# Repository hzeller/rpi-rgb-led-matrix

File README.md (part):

Controlling RGB LED display with Raspberry Pi GPIO
==================================================

A library to control commonly available 128x64, 64x64, 32x32 or 16x32 RGB LED panels
with the Raspberry Pi. Can support PWM up to 11Bit per channel, providing
true 24bpp color with CIE1931 profile.

Supports 3 chains with many panels each on a regular Pi.
On a Raspberry Pi 2 or 3, you can easily chain 12 panels in that chain
(so 36 panels total), but you can theoretically stretch that to up
to 96-ish panels (32 chain length) and still reach
around 100Hz refresh rate with full 24Bit color (theoretical - never tested
this; there might likely be timing problems with the panels that will creep
up then).

With fewer colors or so-called 'outdoor panels' you can control even more,
faster.

The LED-matrix library is (c) Henner Zeller <h.zeller@acm.org>, licensed with
[GNU General Public License Version 2.0 (or any later version)](http://www.gnu.org/licenses/gpl-2.0.txt)
(which means, if you use it in a product somewhere, you need to make the
source and all your modifications available to the receiver of such product so
that they have the freedom to adapt and improve).
Yes, you are also allowed to use
this code under the [GNU General Public License Version 3.0](http://www.gnu.org/licenses/gpl-3.0.txt)
which allows linking with Apache 2.0 code and LGPL-3.0 code.

## Discourse discussion group

**If you'd like help, please do not file a bug, use the discussion board instead:**
https://rpi-rgb-led-matrix.discourse.group/  (obviously please read this whole page first).
If you file a bug asking for personal help instead of using the discourse group, please
state in your bug that you have read this entire page and that you're indeed filing a bug
or request for improvement. Otherwise, please use the discourse group.

Overview
--------
The RGB LED matrix panels can be scored at [Sparkfun][sparkfun],
[AdaFruit][ada] or eBay and Aliexpress. If you are in China, I'd try to get
them directly from some manufacturer, Taobao or Alibaba.

The `RGBMatrix` class provided in `include/led-matrix.h` does what is needed
to control these. You can use this as a library in your own projects or just
use the demo binary provided here which provides some useful examples.

Check out [utils/ directory for some ready-made tools](./utils) to get started
using the library, or the [examples-api-use/](./examples-api-use) directory if
you want to get started programming your own utils.

Panels supported
----------------
This library does not support PWM panels (which actually are better, but need
a completely different driver).\
It should support most other panels with direct addressing (3 to 5 address lines,
ABC for 8x2=16 lines, ABCD for 16x2=32 lines, and ABCDE for 32x2=64 lines).
It also supports panels using shift registers for line addressing, also called ABC
panels up to 64 lines.\
However some amount of panels have uncommon pixel layouts, especially the brighter
panels and may require special pixel mappers (some are called zigzag or zagzig, see
https://rpi-rgb-led-matrix.discourse.group/t/p10rgb-3535-4s-zaggiz-1-4scan-abc-p10-panels-and-https-github-com-2dom-pxmatrix/921 )

Until this wiki has its own confirmed list of working panels, you can refer to
this list: https://github.com/board707/DMD_STM32/wiki/Led_drivers and assume
that all supported panels there should work with this library, or could work
with minimal work to create a pixel mapper.
Please do refer to --led-multiplexing=<0..17> mentioned below and try all values. \
2025/11 update: DMD_STM32 has started adding experimental support for some PWM panels.
These should be labelled as "special" in the table above. They are not supported by this
lib, as it only supports non PWM panels (until someone contributes PWM support).

PWM/E-PWM/S-PWM Panels
----------------------
Newer PWM panels are not currently supported by this lib, but support would really be appreciated.
- https://github.com/hzeller/rpi-rgb-led-matrix/issues/466 - Master bug tracking PWM efforts
- https://github.com/hzeller/rpi-rgb-led-matrix/issues/1866 - Continued discussion

Some experimentation and success has been made with the following fork. Some panel support with FM6373, FM6363, SM16380SH
- https://github.com/kingdo9/rpi-rgb-led-matrix_pwm_experiment

Raspberry Pi 1-5 supported
------------------------------
This library supports the old Raspberry Pi's Version 1 with 26 pin header and
also the B+ models, the Pi Zero, Raspberry Pi 2,3,4 and 5 with 40 pins, as well
as the Compute Modules which have 44 GPIOs.

#### Raspberry Pi 5 support has now been added.
There are two modes to run this on the Pi 5 

**--led-rp1-rio=0** - Uses the Pi 5 coprocessor RP1 to perform the work (default) - Very minimal CPU usage

**--led-rp1-rio=1** - Uses Registered IO block of RP1 to communicate with the GPIO - Higher CPU usage but much faster performance.\
**NOTE: --led-slowdown-gpio** can have the opposite effect in this mode, so going from 2 to 3 may increase performance slightly with --led-rp1-rio=1.

Pi 5 Discussion -  https://github.com/hzeller/rpi-rgb-led-matrix/issues/1603

Thanks to contributions from the following libraries to help implement this.
https://github.com/adafruit/Adafruit_Blinka_Raspberry_Pi5_Piomatter \
https://github.com/bitslip6/rpi-gpu-hub75-matrix \
https://www.i-programmer.info/programming/148-hardware/16887-raspberry-pi-iot-in-c-pi-5-memory-mapped-gpio.html

The 26 pin models can drive one chain of RGB panels, the 40 pin models
**up to three** chains in parallel (each chain 12 or more panels long).
The Compute Module can drive **up to 6 chains in parallel**.
The Raspberry Pi 2 and 3 are faster and generally preferred to the older
models (and the Pi Zero). With the faster models, the panels sometimes
can't keep up with the speed; check out
this [troubleshooting section](#troubleshooting) what to do.

A lightweight, non-GUI, distribution such as [DietPi] is recommended.
[Raspbian Lite][raspbian-lite] is a bit easier to get started with and
is a good second choice.

Types of Displays
-----------------
There are various types of displays that come all with the same Hub75 connector.
They vary in the way the multiplexing is happening so this library supports
options to choose that.
All these are configured by flags (or, programmatically, in an [Options struct](include/led-matrix.h#L57)).

If you have a 64x32 display, you need to supply the flags
`--led-cols=64 --led-rows=32` for instance.

Depending on the Matrix, there are various configuration options that
you might need to set for it to work. See further below in the README for the
[detailed description of these](#changing-parameters-via-command-line-flags).
While the `--led-rows` and `--led-cols` can be derived from simply looking
at the panels, the other options might require some experimenting to find the
right setting if there is no description provided by the manufacturer of
the panel. Going through these options for experiments would typically not do
harm, so you're free to experiment to find your setting.

Flag                                | Description
:---------------      | :-----------------
`--led-cols`          | Columns in the LED matrix, the 'width'.
`--led-rows`          | Rows in the LED matrix, the 'height'.
`--led-multiplexing`  | In particular bright outdoor panels with small multiplex ratios require this. Often an indicator: if there are fewer address lines than expected: ABC (instead of ABCD) for 32 high panels and ABCD (instead of ABCDE) for 64 high panels.
`--led-row-addr-type` | Addressing of rows; in particular panels with only AB address lines might indicate that this is needed.
`--led-panel-type`    | Chipset of the panel. In particular if it doesn't light up at all, you might need to play with this option because it indicates that the panel requires a particular initialization sequence.

Panels can be chained by connecting the output of one panel to the input of
the next panel. You can chain quite a few together, but the refresh rate will
reduce with longer chains.

The 64x64 matrixes typically come in two kinds: with 5 address
lines (A, B, C, D, E), or (A, B); the latter needs a `--led-row-addr-type=1`
parameter. So-called 'outdoor panels' are typically brighter and allow for
faster refresh-rate for the same size, but do some multiplexing internally
of which there are a few types out there; they can be chosen with
the `--led-multiplexing` parameter.
Many 128x64 panels now use ABC addressing using shift registers, instead of direct
ABCDE addressing. Look at using --led-row-addr-type=5 or --led-row-addr-type=3
with them (and you may need to use --led-slowdown-gpio of 2 or more. Please
see this bug for more details: https://github.com/hzeller/rpi-rgb-led-matrix/issues/1774

There are some panels that have a different chip-set than the default HUB75.
These require some initialization sequence. The current supported types are
`--led-panel-type=FM6126A` and `--led-panel-type=FM6127`.

Generally, the higher scan-rate (e.g. 1:8), a.k.a. outdoor panels generally
allow faster refresh rate, but you might need to figure out the multiplexing
mapping if one of the three provided does not work.

Some 32x16 outdoor matrixes with 1:4 scan (e.g. [Qiangli Q10(1/4) or X10(1/4)](http://qiangliled.com/products-63.html))
have 4 address line (A, B, C, D). For such matrices is necessary to
use `--led-row-addr-type=2` parameter. Also the matrix Qiangli Q10(1/4)
have "Z"-stripe pixel mapping and in this case, you'd use two parameters
at the same time `--led-row-addr-type=2 --led-multiplexing=4`.

Sub-Pages
---------
This documentation is split into parts that help you through the process

- 
    [**Wire up the matrix to your Pi**](./wiring.md). This document describes
    what goes where.
- [How to map pixels between panels or within panels](./lib). This is crucial for figuring out pixel mappers,
  matrix mappers and so forth. This is where you will learn about panel layout with U-Mapper, V-Mapper, V-Mapper:Z
- [Adapter GPIO boards output to up to 3 channels (electrodragon board recommended)](./adapter).
    If you have an [Adafruit HAT] or [Adafruit Bonnet], you can choose that with
    a command line option [described below](#if-you-have-an-adafruit-hat-or-bonnet)
- [All the command line options you can give to demo and in turn use in your library code](./examples-api-use).
- [Installing an Optimized Kernel to fix most flickering issues](./optimized-kernel)

Python Support
--------------
The python bindings have been overhauled as of February 2026 and are now built with scikit-build-core and cmake. While
this update has been tested there are likely edge cases that have not been caught. Please subscribe to the master Python
bug to assist or check for the latest updates.
https://github.com/hzeller/rpi-rgb-led-matrix/issues/1749.

The entire repository itself is PIP-able and can be installed as a package directly. Python dev packages are required.
```
sudo apt-get install python-dev-is-python3 python3-pil cython3
pip install git+https://github.com/hzeller/rpi-rgb-led-matrix
```

Rpi Hardware Support
--------------------
While this code should still work on rPi1 or Rpi0, those are underpowered and not recommended. An ESP32 is cheaper and faster.
Rpi2 is honestly old and slow too.
Rpi3 / Rpi3a / Rpi0 2wl will work for most displays but will be slow if you are rotating a huge display in a mapper (Rpi0 2wl is a slightly faster version of Rpi3)
Rpi4 is the fastest supported chip which will need a higher slowdown gpio value to avoid overwhelming panels (if they display garbage)
Rpi5 is not officially supported as of 2025/11, but see https://github.com/hzeller/rpi-rgb-led-matrix/issues/1603

Let's do it
------------
  1. Run a demo. You find that in the
     [examples-api-use/](./examples-api-use#running-some-demos) directory:
```
make -C examples-api-use
sudo examples-api-use/demo -D0
```
  2. Use the utilities. The [utils](./utils) directory has some ready-made
    useful utilities to show content. [Go there](./utils) to see how to
    compile and run these.
  3. Write your own programs using the Matrix in C++ or one of the
     bindings such as Python or C#.

### Wiring / Boards

Please see the [Adadpter Boards or Self Wiring](./adapter).

Summary is:
- Yes you can self wire without level shifters and it will work most of the time, but if you're not in a hurry get a board
- https://www.electrodragon.com/product/rgb-matrix-panel-drive-board-for-raspberry-pi-v2/ **is the recommended solution with 3 channels and level shifters**. You can't go wrong there, but expect a bit of shipping time.
- If shipping time is crucial and you don't want to wire your own, Adafruit sells a single channel board (the electrodragon one is 3 channels), but note that its wiring is non standard and requires a special compile option or command line argument: https://www.adafruit.com/product/3211

### Utilities

The [utils directory](./utils) is meant for ready utilities to show images or
animated gifs or videos. Read the [README](./utils/README.md) there for
instructions how to compile.

There are external projects that use this library and provide higher level
network protocols, such as the
 * [FlaschenTaschen implementation](https://github.com/hzeller/flaschen-taschen)
   (VLC can send videos to it natively)
 * [PixelPusher implementation](https://github.com/hzeller/rpi-matrix-pixelpusher) (common in light art installations)
 * [ZeroMQ-server](https://github.com/Knifa/led-matrix-zmq-server) to receive
   content.
 * Marc's [FastLED_RPIRGBPanel_GFX](http://marc.merlins.org/perso/arduino/post_2020-01-01_Running-FastLED_-Adafruit_GFX_-and-LEDMatrix-code-on-High-Resolution-RGBPanels-with-a-Raspberry-Pi.html) allows running arduino code on linux/rPi and display on bigger RGBPanel matrices than arduino chips, can.

### API

The library comes as an API that you can use for your own utilities and use-cases.

  * The native library is a C++ library (see [include/](./include)).
    Example uses you find in the [examples-api-use/](./examples-api-use)
    directory.
  * If you prefer to program in C, there is also a
    [C API](./include/led-matrix-c.h).
  * In the [python](./bindings/python) subdirectory, you find a Python API including a
    couple of [examples](./bindings/python/samples) to get started.
  * There are a couple of external bindings, such as
      * [Nodejs binding] by Maxime Journaux
      * [Nodejs/Typescript binding] by Alex Eden
      * [Go binding] by Máximo Cuadros
      * [Rust binding] by Vincent Pasquier

### Changing parameters via command-line flags

For the programs in this distribution and also automatically in your own
programs using this library, there are a lot of parameters provided as command
line flags, so that you don't have to re-compile your programs to tweak them.
Some might need to be changed for your particular kind of panel.

Here is a little run-down of what these command-line flags do and when you'd
like to change them.

First things first: if you have a different wiring than described in
[wiring](./wiring.md), for instance if you have an Adafruit HAT/Bonnet, you can
choose these here:

```
--led-gpio-mapping=<gpio-mapping>: Name of GPIO mapping used. Default "regular"
```

This can have values such as
  - `--led-gpio-mapping=regular` The standard mapping of this library, described in the [wiring](./wiring.md) page.
  - `--led-gpio-mapping=adafruit-hat` The Adafruit HAT/Bonnet, that uses this library or
  - `--led-gpio-mapping=adafruit-hat-pwm` Adafruit HAT with the anti- hardware mod [described below](#improving-flicker-hardware-patch).
  - `--led-gpio-mapping=compute-module` Additional 3 parallel chains can be used with the Compute Module.

Learn more about the mappings in the [wiring documentation](wiring.md#alternative-hardware-mappings).

#### GPIO speed

```
--led-slowdown-gpio=<0..10>: Slowdown GPIO. Needed for faster Pis and/or slower panels (Default: 1).
```

The Raspberry Pi starting with Pi2 are putting out data too fast for almost
all LED panels I have seen. In this case, you want to slow down writing to
GPIO. Zero for this parameter means 'no slowdown'.

The default 1 (one) typically works fine, but often you have to even go further
by setting it to 2 (two). If you have a Raspberry Pi with a slower processor
(Model A, A+, B+, Zero), then a value of 0 (zero) might work and is desirable.

If you find yourself needing very high values of slowdown like 8 for ABC 128x64 panels,
do try --led-row-addr-type=5 instead of --led-row-addr-type=3. Details in this bug:
https://github.com/hzeller/rpi-rgb-led-matrix/issues/1773

A Raspberry Pi 3 or Pi4 might even need higher values for the panels to be
happy.

#### Panel Connection
The next most important flags describe the type and number of displays connected

```
--led-rows=<rows>        : Panel rows. Typically 8, 16, 32 or 64. (Default: 32).
--led-cols=<cols>        : Panel columns. Typically 32 or 64. (Default: 32).
--led-chain=<chained>    : Number of daisy-chained panels. (Default: 1).
--led-parallel=<parallel>: For A/B+ models or RPi2,3b: parallel chains. range=1..3 (Default: 1, 6 for Compute Module).
```

These are the most important ones: here you choose how many panels you have
connected and how many rows are in each panel. Panels can be chained (each panel
has an input and output connector, see the
[wiring documentation](wiring.md#chains)) -- the `--led-chain` flag tells the
library how many panels are chained together. The newer Raspberry Pi's allow
to connect multiple chains in parallel, the `--led-parallel` flag tells it how
many there are.

This illustrates what each of these parameters mean:

##### Panel Type

Typically, panels should just work out of the box, but some panels use a
different chip-set that requires some initialization. If you don't see any
output on your panel, try setting:

```
--led-panel-type=FM6126A
```

Some panels have the FM6127 chip, which is also an option.

##### Multiplexing
If you have some 'outdoor' panels or panels with different multiplexing,
the following will be useful:

```
--led-multiplexing=<0..17> : Mux type: 0=direct; 1=Stripe; 2=Checkered...
```

The outdoor panels have different multiplexing which allows them to be faster
and brighter, but by default their output looks jumbled up.
They require some pixel-mapping of which there are a few
types you can try and hopefully one of them works for your panel; The default=0
is no mapping ('standard' panels), while 1, 2, ... are different mappings
to try with. If your panel has a different mapping, you find everything you
need to implement one in [lib/multiplex-mappers.cc](lib/multiplex-mappers.cc).
Please send a pull request if you encounter a panel for which you needed to
implement a new mapping.

Note that you have to set the `--led-rows` and `--led-cols` to the rows and
columns that are physically on each chained panel so that the multiplexing
option can work properly. For instance a `32x16` panel with `1:4` multiplexing
would be controlled with `--led-rows=16 --led-cols=32 --led-multiplexing=1` (or
whatever multiplexing type your panel is, so it can also be `--led-multiplexing=2` ...).

For `64x32` panels with `1:8` multiplexing, this would typically be
`--led-rows=32 --led-cols=64 --led-multiplexing=1`;
however, there are some panels that internally behave like
two chained panels, so then you'd use
`--led-rows=32 --led-cols=32 --led-chain=2 --led-multiplexing=1`;

```
--led-row-addr-type=<0..5>: 0 = default; 1 = AB-addressed panels; 2 = direct row select; 3 = ABC-addressed panels; 4 = ABC Shift + DE direct, 5 = ABC method similar to 3, but faster on some panels (needs less of a slowdown) (Default: 0).
```

This option is useful for certain 64x64 or 32x16 panels. For 64x64 panels,
that only have an `A` and `B` address line, you'd use `--led-row-addr-type=1`.
This is only tested with one panel so far, so if it doesn't work for you,
please send a pull request.

For 32x16 outdoor panels, that have have 4 address line (A, B, C, D), it is
necessary to use `--led-row-addr-type=2`.

Performance improvements and limits, Maximizing refresh rate, ABC vs ABCDE, row-addr-type=5 vs 3
-------------------------------------------------------------------------------------------------
Regardless of which driving hardware you use, ultimately you can only push pixels
so fast to a string of panels before you get flickering due to too low a refresh
rate (less than 80-100Hz), or before you refresh the panel lines too fast and they
appear too dim because each line is not displayed long enough before it is turned off.

Basic performance tips:
- Use --led-show-refresh to see the refresh rate while you try parameters
- use an active-3 board with led-parallel=3 any time possible instead of chaining panels.
- led-pwm-dither-bits=1 gives you a speed boost but potentially less brightness
- led-pwm-lsb-nanoseconds=50 also gives you a speed boost but may lead to less brightness
- led-pwm-bits=7 or even lower decrease color depth but increases refresh speed
- AB panels and other panels with that use values of led-multiplexing bigger than 0,
will also go faster, although as you tune more options given above, their advantage will decrease.
- 32x16 ABC panels are faster than ABCD which are faster than ABCDE, which are faster than 128x64 ABC panels
(which do use 5 address lines, but over only 3 wires)
- For 128x64 ABC speed on shift registers vs ABCDE
- Use at least an rPi3 (rPi4 is still slightly faster but may need --led-slowdown-gpio=2)

Maximizing refresh rate to 300 or even 400Mhz refresh for 3x 128x64 panels:
- ABCDE panels will allow for faster refresh rate than ABC panels because they can be run with
lower --led-slowdown-gpio=1 (which may need to be 2 for ABCDE) on rPi3 (rPi4 may require bigger
slowdowns. You may even end up in a situation where a Pi3 will give you faster refresh than a Pi4
by needing smaller slowdowns
- To achieve 410Hz refresh for 3x 128x64 direct ABCDE panels, use this "~/rpi-rgb-led-matrix/examples-api-use/demo --led-rows=64 --led-cols=128 --led-chain=1 --led-parallel=3 --led-show-refresh --led-scan-mode=0 --led-pwm-bits=7 --led-pwm-lsb-nanoseconds=50 --led-pwm-dither-bits=1 -D0  --led-row-addr-type=0 --led-slowdown-gpio=1"
- To achieve 350hz refresh for 3x 128x64 shift register panels, use this: "~/rpi-rgb-led-matrix/examples-api-use/demo --led-rows=64 --led-cols=128 --led-chain=1 --led-parallel=3 --led-show-refresh --led-scan-mode=0 --led-pwm-bits=7 --led-pwm-lsb-nanoseconds=50 --led-pwm-dither-bits=1 -D0  --led-row-addr-type=5 --led-slowdown-gpio=2"

Please see this bug for discussion of ABC vs ABCDE and using --led-row-addr-type=5 instead of --led-row-addr-type=3:
https://github.com/hzeller/rpi-rgb-led-matrix/issues/1774#issuecomment-2860617056

Maximum resolutions reasonably achievable:
A general rule of thumb is that running 16K pixels (128x128 or otherwise) on a single chain,
is already pushing limits and you will have to make tradeoffs in visual quality. 32K pixels
(like 128x256) is definitely pushing things and you'll get 100Hz or less depending on the
performance options you choose.
This puts the maximum reasonable resolution around 100K pixels (like 384x256) for 3 chains.
You can see more examples and video capture of speed on [Marc MERLIN's page 'RGB Panels, from 192x80, to 384x192, to 384x256 and maybe not much beyond'](http://marc.merlins.org/perso/arduino/post_2020-03-13_RGB-Panels_-from-192x80_-to-384x192_-to-384x256-and-maybe-not-much-beyond.html)
If your refresh rate is below 300Hz, expect likely black bars when taking cell phone pictures.
A real camera with shutter speed lowered accordingly, will get around this.

Ultimately, you should not expect to go past 64K pixels using 3 chains without significant
quality tradeoffs. If you need bigger displays, you should use multiple boards and synchronize the
output.

#### Panel Arrangement

```
--led-pixel-mapper  : Semicolon-separated list of pixel-mappers to arrange pixels.
```

Optional params after a colon e.g. "U-mapper;Rotate:90"

Available | Parameter after colon| Example
----------|----------------------|----------
Mirror    | `H` or `V` for horizontal/vertical mirror. | `Mirror:H`
Rotate    | Degrees.                                   | `Rotate:90`
U-mapper  | -

Mapping the logical layout of your boards to your physical arrangement. See
more in [Remapping coordinates](./examples-api-use#remapping-coordinates).

#### Misc Options

```
--led-brightness=<percent>: Brightness in percent (Default: 100).
```

Self explanatory.

```
--led-pwm-bits=<1..11>    : PWM bits (Default: 11).
```

The LEDs can only be switched on or off, so the shaded brightness perception
is achieved via PWM (Pulse Width Modulation). In order to get a good 8 Bit
per color resolution (24Bit RGB), the 11 bits default per color are good
(why ? Because our eyes are actually perceiving brightness logarithmically, so
we need a lot more physical resolution to get 24Bit sRGB).

With this flag, you can change how many bits it should use for this; lowering it
means the lower bits (=more subtle color nuances) are omitted.
Typically you might be mostly interested in the extremes: 1 Bit for situations
that only require 8 colors (e.g. for high contrast text displays) or 11 Bit
for everything else (e.g. showing images or videos). Why would you bother at all ?
Lower number of bits use slightly less CPU and result in a higher refresh rate.

```
--led-show-refresh        : Show refresh rate.
```

This shows the current refresh rate of the LED panel, the time to refresh
a full picture. Typically, you want this number to be pretty high, because the
human eye is pretty sensitive to flicker. Depending on the settings, the
refresh rate with this library are typically in the hundreds of Hertz but
can drop low with very long chains. Humans have different levels of perceiving
flicker - some are fine with 100Hz refresh, others need 250Hz.
So if you are curious, this gives you the number (shown on the terminal).

The refresh rate depends on a lot of factors, from `--led-rows` and `--led-chain`
to `--led-pwm-bits`, `--led-pwm-lsb-nanoseconds` and `--led-pwm-dither-bits`.
If you are tweaking these parameters, showing the refresh rate can be a
useful tool.

```
--led-limit-refresh=<Hz>  : Limit refresh rate to this frequency in Hz. Useful to keep a
                            constant refresh rate on loaded system. 0=no limit. Default: 0
```

This allows to limit the refresh rate to a particular frequency to approach
a fixed refresh rate.

This can be used to mitigate some situations in which you have a faint flicker,
which can happen due to hardware events (network access)
or other situations such as other IO or heavy memory access by other
processes. Also when you see wildly changing refresh frequencies with
`--led-show-refresh`.

You trade a slightly slower refresh rate and display brightness for less
visible flicker situations.

For this to calibrate, run your program for a while with --led-show-refresh
and watch the line that shows the current refresh rate and minimum refresh
rate observed. So wait a while until that value doesn't
change anymore (e.g. a minute, so that you catch tasks that happen once
a minute, such as ntp updated).
Use this as a guidance what value to choose with `--led-limit-refresh`.

The refresh rate will now be adapted to always reach this value
between frames, so faster refreshes will be slowed down, but the occasional
delayed frame will fit into the time-window as well, thus reducing visible
brightness fluctuations.

You can play with value a little and reduce until you find a good balance
between refresh rate and flicker suppression.

Use this also if you want to have a stable baseline refresh rate when using
the vsync-multiple flag `-V` in the [led-image-viewer] or
[video-viewer] utility programs.

```
--led-no-busy-waiting     : Don't use busy waiting when limiting refresh rate.
```

This allows to switch from busy waiting to sleep waiting when limiting the
refresh rate (`--led-limit-refresh`).

By default, refresh rate limiting uses busy waiting, which is CPU intensive but
gives most accurate timings. This is fine for multi-core boards.

On single core boards (e.g.: Raspberry Pi Zero) busy waiting makes the system
unresponsive for other/background tasks. There, sleep waiting improves the
system's responsiveness at the cost of slightly less accurate timings.

```
--led-scan-mode=<0..1>    : 0 = progressive; 1 = interlaced (Default: 0).
```

This switches from progressive scan and interlaced scan. The latter might
look be a little nicer when you have a very low refresh rate, but typically
it is more annoying because of the comb-effect (remember 80ies TV ?).

```
--led-pwm-lsb-nanoseconds : PWM Nanoseconds for LSB (Default: 130)
```

This allows to change the base time-unit for the on-time in the lowest
significant bit in nanoseconds.
Lower values will allow higher frame-rate, but will also negatively impact
qualty in some panels (less accurate color or more ghosting).

Good values for full-color display (PWM=11) are somewhere between 100 and 300.

If you you use reduced bit color (e.g. PWM=1) and have sharp contrast
applications, then higher values might be good to minimize ghosting.

How to decide ? Just leave the default if things are fine. But some panels have
trouble with sharp contrasts and short pulses that results
in ghosting. It is particularly apparent in situations such as bright text
on black background. In these cases increase the value until you don't see
this ghosting anymore.

The following example shows how this might look like:

Ghosting with low --led-pwm-lsb-nanoseconds  | No ghosting after tweaking
---------------------------------------------|------------------------------
                   |

If you tweak this value, watch the framerate (`--led-show-refresh`) while playing
with this number.

```
--led-pwm-dither-bits   : Time dithering of lower bits (Default: 0)
```

The lower bits can be time dithered, i.e. their brightness contribution is
achieved by only showing them some frames (this is possible,
because the PWM is implemented as binary code modulation).
This will allow higher refresh rate (or same refresh rate with increased
`--led-pwm-lsb-nanoseconds`).
The disadvantage could be slightly lower brightness, in particular for longer
chains, and higher CPU use.
CPU use is not of concern for Raspberry Pi 2 or 3 (as we run on a dedicated
core anyway) but probably for Raspberry Pi 1 or Pi Zero.
Default: no dithering; if you have a Pi 3 and struggle with low frame-rate due
to high multiplexing panels (1:16 or 1:32) or long chains, it might be
worthwhile to try.

```
--led-no-hardware-pulse   : Don't use hardware pin-pulse generation.
```

This library uses a hardware subsystem that also is used by the sound. You can't
use them together. If your panel does not work, this might be a good start
to debug if it has something to do with the sound subsystem (see Troubleshooting
section). This is really only recommended for debugging; typically you actually
want the hardware pulses as it results in a much more stable picture.

```
--led-no-drop-privs       : Don't drop privileges from 'root' after initializing the hardware.
```

You need to start programs as root as it needs to access some low-level hardware
at initialization time. After that, it is typically not desirable to stay in this
role, so the library then drops the privileges.

This flag allows to switch off this behavior, so that you stay root.
Not recommended unless you have a specific reason for it (e.g. you need root
to access other hardware or you do the privilege dropping yourself).

```
--led-daemon              : Make the process run in the background as daemon.
```

If this is set, the program puts itself into the background (running
as 'daemon').
You might want this if started from an init script at boot-time.

```
--led-inverse             : Switch if your matrix has inverse colors on.
--led-rgb-sequence        : Switch if your matrix has led colors swapped (Default: "RGB")
```

These are if you have a different kind of LED panel in which the logic of the
color bits is reversed (`--led-inverse`) or where the Red, Green and Blue LEDs
are mixed up (`--led-rgb-sequence`). You know it when you see it.

Troubleshooting
---------------
Here are some tips in case things don't work as expected.

### Use minimal Raspbian distribution
In general, run a minimal configuration on your Pi.
  
  * Common cause for flickering \
    **Ensure 5V is getting to LED Display and Raspberry Pi devices !!** \
    Use a Multimeter to check, also use dmesg command to check for any Raspberry Pi undervolt messages.\
    It may be best to power the LED Display externally especially if using Raspberry Pi 4.

    Additionally see [Installing an Optimized Kernel to fix most flickering issues](./optimized-kernel)

  * Do not use a graphical user interface (Even though the
    Raspberry Pi foundation makes you believe that you can do that: don't.
    Using a Pi with a GUI is a frustratingly slow use of an otherwise
    perfectly good embedded device.).
    Always operate your Raspberry Pi [headless].

  * Switch off on-board sound
    (`dtparam=audio=off` in `/boot/config.txt` pre-bookworm)
    (`dtparam=audio=off` in `/boot/firmware/config.txt` post-bookworm)
    External USB sound adapters work, and are much better quality anyway,
    so that is recommended if you happen to need sound. The on-board sound
    uses a timing circuit that the RGB-Matrix needs (it seems in some
    distributions, such as arch-linux, this is not enough and you need
    to explicitly blacklist the snd_bcm2835 module).\     
    
    post-bookworm \
    nano /etc/modprobe.d/blacklist-audio.conf \
    blacklist snd_bcm2835 \
    CTRL+S CTRL+X to Save File and Exit

  * Don't run anything that messes in parallel with the GPIO pins, e.g.
    PiGPIO library/daemon or devices that use the i2c or 1-wire interface if
    they are on the same pins you need for the panel.

  * I have also seen reports that on some Pis, the one-wire protocol is
    enabled (w1-gpio). This will also not work (disable by removing
    `dtoverlay=w1-gpio` in `/boot/config.txt` (pre-bookworm) or in
    `/boot/firmware/config.txt` (post-bookworm); or using `raspi-config`,
    Interface Options -> 1-Wire)

  * If you see some regular flickering, make sure that there is no other
    process running on the system that could cause that. For instance, it is
    known that merely running `top` creates a faint flicker every second it
    updates. Or a regular ntp run can also cause flicker once a minute
    (switch off with `sudo timedatectl set-ntp false`). Maybe instead you
    might want to run ntp at system start-up but then not regularly updating.
    There might be other things running regularly you don't need;
    consider a `sudo systemctl stop cron` for instance.
    To address some irregular flicker, consider the
    [`--led-limit-refresh`](#misc-options) option.

  * There are probably other processes that are running that you don't need
    and remove them; I usually remove right away stuff I really don't need e.g.
    ```
    sudo apt-get remove bluez bluez-firmware pi-bluetooth triggerhappy pigpio
    ```
    Take a close look at your systemd (`systemctl`) and see if there are other
    things running you don't need. If you have seen packages in standard
    Raspbians that interfere with the matrix code, let me know to include it
    here.
    In general: This is why starting with a minimal installation is a good
    idea: there is simply less cruft that you have to disable.

  * When attempting to connect sensors like the DHT22 to available GPIO pins
    and display their results on your LED panel, you might encounter an issue
    where the sensors fail to provide any data due to the Raspberry Pi resource
    limitations. This situation is particularly evident on older models like the
    Raspberry Pi 1 B. To address this, it is advisable to select a Raspberry Pi
    model with higher resources to ensure proper functionality.

The default install of **[Raspbian Lite][raspbian-lite]** or **[DietPi]**
seem to be good starting points, as they have a reasonably minimal
configuration to begin with. Raspbian Lite is not as lite anymore
as it used to be; I prefer DietPi these days. Note that any of the above
changes to `/boot/...` must be applied to `/boot/firmware/...` if you are on a
non-Raspbian distro (e.g. Ubuntu for ARM).

### Bad interaction with Sound
If sound is enabled on your Pi, this will not work together with the LED matrix,
as both need the same internal hardware sub-system (a first test to see if you
are affected is to run the progrem with `--led-no-hardware-pulse` and see if
things work fine then).

If you run `lsmod` and see the `snd_bcm2835` module, this could be causing trouble.
(The library actually exits if it finds this module to be loaded).

In that case, you should create a kernel module blacklist file like the
following on your system and update your initramfs:

```
cat <<EOF | sudo tee /etc/modprobe.d/blacklist-rgb-matrix.conf
blacklist snd_bcm2835
EOF

sudo update-initramfs -u
```

Reboot and confirm that the module is not loaded.

### I have followed some tutorial on the Internet and it doesn't work

Well, if you use this library, please read the documentation provided _here_,
not on some other website. Most important for you to get started
is the [wiring guide](./wiring.md). There are some tutorials floating around
that refer to a very old version of this library.

### I have a Pi1 Revision1 and top part of Panel doesn't show green

Use `--led-gpio-mapping=regular-pi1`

### Logic level voltage not sufficient
Some panels don't interpret the 3.3V logic level well, or the RPi output drivers
have trouble driving longer cables, in particular with
faster Raspberry Pis Version 2. This results in artifacts like randomly
showing up pixels, color fringes, or parts of the panel showing 'static'.

If you encounter this, try these things

   - Make sure to have as short as possible flat-cables connecting your
     Raspberry Pi with the LED panel.

   - In particular if the chips close to the input of the LED panel
     read 74HC245 instead of 74HCT245 or 74AHCT245, then this board will not
     work properly with 3.3V inputs coming from the Pi.
     Use an [adapter board](./adapter/active-3) with a bus-driver that acts as
     level shifter between 3.3V and 5V.
     (In any case, it is always a good idea to use the level shifters).

   - A temporary hack to make HC245 inputs work with the 3.3V levels is to
     supply only like 4V to the LED panel. But the colors will be off, so not
     really useable as long-term solution.

   - If you can't implement the above things, or still have problems, you can
     slow down the GPIO writing a bit. This will of course reduce the
     frame-rate, so it comes at a cost.

For GPIO slow-down, add the flag `--led-slowdown-gpio=2` to the invocation of
the binary.

If you have an Adafruit HAT or Bonnet
---------------------------

Generally, if you want to connect RGB panels via an adapter instead of
hand-wiring, I suggest to build one of the adapters whose open-hardware
files you find in the [adapter/](./adapter) subdirectory. It is a fun solder
exercise with large surface mount components.

However, Adafruit [offers an adapter][adafruit-hat] which is already ready-made,
but it only allows for a single chain. If the
ready-made vs. single-chain tradeoff is worthwhile, then you might go for that
(I am not affiliated with Adafruit).

### Switch the Pinout

The Adafruit HAT/Bonnet uses this library but a modified pinout to support other
features on the HAT. You can choose the Adafruit pinout with a command line
flag.

Just pass the option `--led-gpio-mapping=adafruit-hat`. This works on the C++
and Python examples.

### Improving flicker: hardware patch

To improve flicker, we need to do a little hardware modification,
but it is very simple: solder a wire between GPIO 4 and 18 as shown in the
following picture (click to enlarge):

Then, start your programs with `--led-gpio-mapping=adafruit-hat-pwm`.

Now you should have less visible flicker. This essentially
switches on the hardware pulses feature for the Adafruit HAT/Bonnet.

### Improving flicker: Optimized Kernel
See [Installing an Optimized Kernel to fix most flickering issues](./optimized-kernel)

### 64x64 with E-line on Adafruit HAT/Bonnet
There are LED panels that have 64x64 LEDs packed, but they need 5 address lines,
which is 1:32 multiplexing (they have an `E` address-line). The first generation
of the Adafruit HAT/Bonnet was not prepared for this, but it can be done with another
hardware mod. Beginning October 2018, Adafruit began selling an updated version of
the HAT that supports 64x64 panels simply by bridging two pads on the PCB with solder.

You can identify which HAT you have by looking for the **Address E** pads, circled here:

### New Adafruit RGB Matrix Hat (with Address E pads)

Look for the Address E pads located between the HUB75 connector and Pi camera cutout.

Melt a blob of solder between the center “E” pad the the “8” pad just above it
(for 64x64 matrices in the Adafruit shop)…*_or_* the “16” pad below (rare, for some
third-party 64x64 matrices…check datasheet).

### Old Adafruit HAT/Bonnet (without)

Newer HAT/Bonnet versions have a special pad for the E-line next to the IDC socket
which makes this mod easily doable with a bit of solder. For details, refer to
[the Adafruit page on driving matrices](https://learn.adafruit.com/adafruit-rgb-matrix-plus-real-time-clock-hat-for-raspberry-pi/driving-matrices).

For older HATs, the only option is a little more advanced hack, so it's only really
for people who are comfortable with this kind of thing.
First, you have to figure out which is the input of the E-Line on your matrix
(they seem to be either on Pin 4 or Pin 8 of the IDC connector).
You need to disconnect that Pin from the ground plane (e.g. with an Exacto
knife) and connect GPIO 24 to it. The following images illustrate the case for
IDC Pin 4.

If the direct connection does not work, you need to send it through a free
level converter of the Adafruit HAT/Bonnet. Since all unused inputs are grounded
with traces under the chip, this involves lifting a leg from the
HCT245 (figure out a free bus driver from the schematic). If all of the
above makes sense to you, you have the Ninja level to do it!

It might be more convenient at this point to consider the [Active3 adapter](./adapter/active-3)
that has that covered already.

Running as root
---------------
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
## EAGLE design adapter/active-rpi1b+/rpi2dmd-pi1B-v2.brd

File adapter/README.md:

PCB adapter for Raspberry Pi to Hub75 RGB Matrixes
==================================================

Since hand-wiring can be a little tedious, here are some PCBs that help
with the wiring when using the `rpi-rgb-led-matrix` code.

![Three Panels connected][three-panels]

[three-panels]: ../img/three-parallel-panels-soic.jpg

   * [Passive-3](./passive-3) Supports three parallel chains, directly connected
     to the output of a Raspberry Pi with 40 GPIO pins. Works, but usually it is better to
     buffer the outputs using the ...
   * [Active-3](./active-3) board. Supports three parallel chains with active buffering
     and 3.3V -> 5V level shifting for best reliability. Requires SMD soldering.
     
     As another option you can buy it from these locations not affiliated with this project.
     They are given to help you locate premade boards but no guarantees are given or implied:
     * https://www.electrodragon.com/product/rgb-matrix-panel-drive-board-raspberry-pi/
       ($3/board, but fairly long and/or expensive shipping from HKG). The old board includes 
       support for an optional RTC (real time clock) which had to be disabled for most users 
       who wanted 3 channels instead of an RTC.
     * The new HD board with angled connectors (thinner footprint), is here: https://www.electrodragon.com/product/rgb-matrix-panel-drive-board-for-raspberry-pi-v2/ << **this is the recommended board for most users today**  (or consider the smaller adafruit active-3 board below)

     * If you have an rpi0 2wl, this passive board was made specifically to be as small as possible: https://www.electrodragon.com/product/rpi-passive-3ch-rgb-matrix-drive-board-v0/

   * After the passive-3 low profile board from Electrodragon, Adafruit made an even better version that is about the same size, but active-3, which may work slightly better and faster with some panels. Its only small potential downside is the connectors are pointed up as opposed to sideways, so the entire thing will be a bit taller compared to the ED3 board, due to cables pointing up, but it's minor and active-3 is a win, so this is definitely a recommended board: https://www.adafruit.com/product/6358  

   * Another ready-to-use active-3 adapter is available also from Acme Systems ( https://www.acmesystems.it/HAT-A3 )

   * The [Passive-RPi1](./passive-rpi1) adapter board is to connect one panel to
     Raspberry Pi 1 with 26 GPIO pins.

   * For completeness, Adafruit has a single channel active board here: 
     https://www.adafruit.com/product/3211 although it is ultimately inferior to the electrodragon board, but it does ship quicker if you're in the US (note that you will need special compile option or command line argument since it uses non standard wiring). Please prefer this new adafruit version that is triple output with the standard pin mapping: https://www.adafruit.com/product/6358

   * As of 2024/12 and this thread: https://rpi-rgb-led-matrix.discourse.group/t/solved-aliexpress-2-string-passive-adapter-not-working-because-rpi-connector-was-soldered-on-the-wrong-side-of-the-board/892/26 , there is also a cheap passive 2 channel board that works great on a small board like rPi0 2W, but all chinese sellers that Marc Merlin surveyed at the time, sold the board soldered wrong and they do not work unless you order the board unsoldered and solder it yourself. Electrodragon made a low profile 3 channel passive board that is a proper replacement for the unnamed mis-soldered chinese board while offering 3 channels (see above). In short, do not buy that one

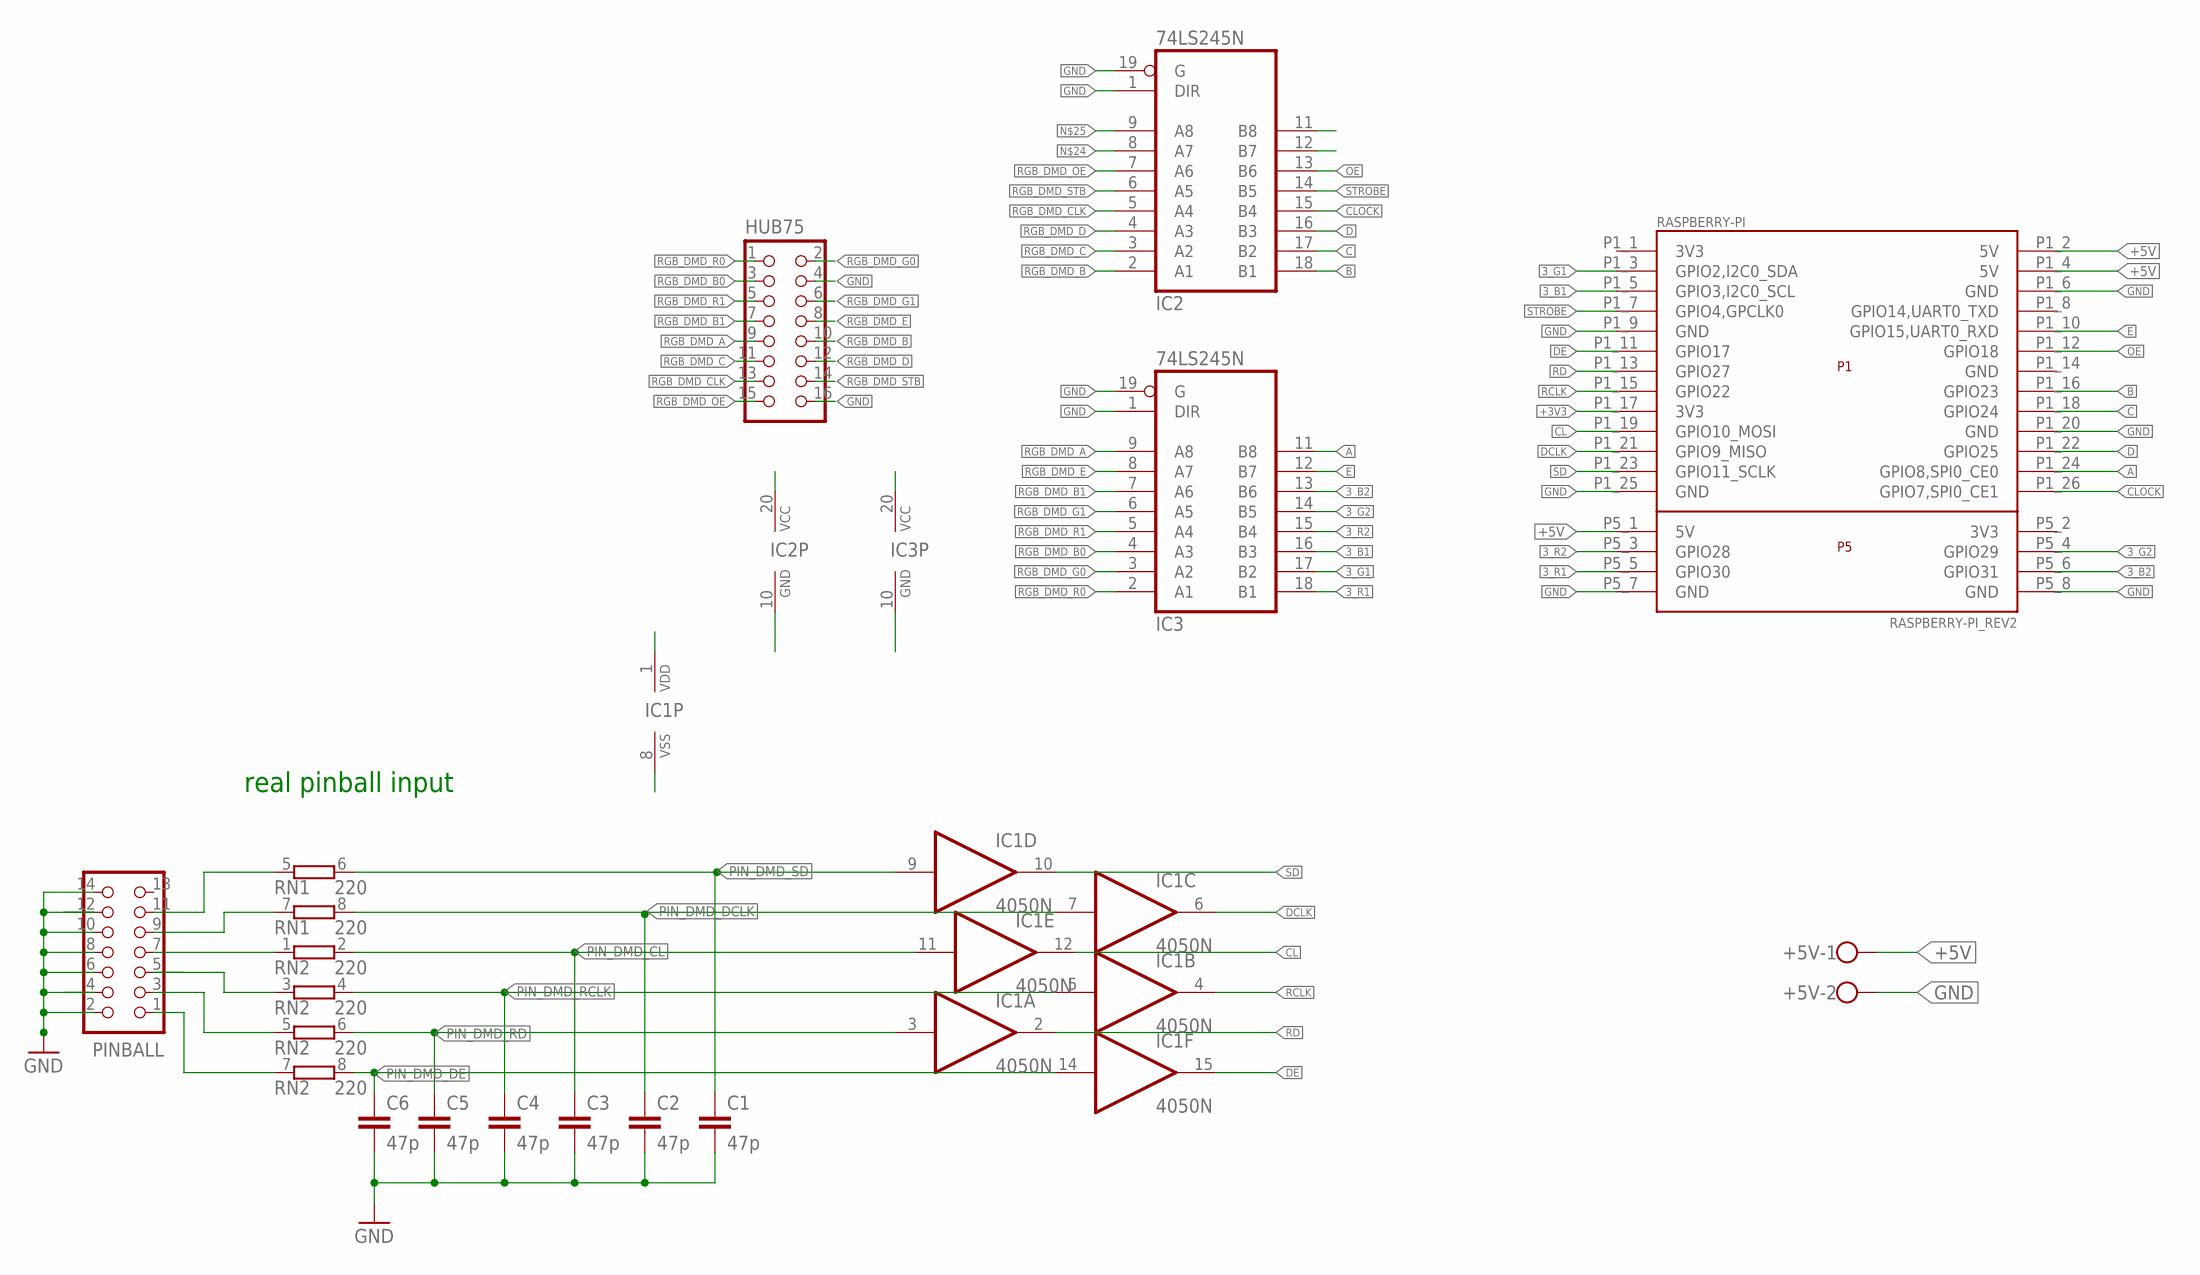
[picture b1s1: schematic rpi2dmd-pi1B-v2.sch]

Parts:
+5V: W237-102
C1, C2, C3, C4, C5, C6: 47p; C025-024X044
HUB75: CON_HEADER_2X08B; PINSHRD_PTH_2X08
IC1: 4050N; DIL16
IC2, IC3: 74LS245N; DIL20
PINBALL: CON_HEADER_2X07-PTH-SHROUDED; PINSHRD_PTH_2X07
RASPBERRY-PI: RASPBERRY-PI_REV2
RN1, RN2: 220; SIL8

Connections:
3_B1: IC3.16 (B3), RASPBERRY-PI.P1_5 (GPIO3,I2C0_SCL)
3_B2: IC3.13 (B6), RASPBERRY-PI.P5_6 (GPIO31)
3_G1: IC3.17 (B2), RASPBERRY-PI.P1_3 (GPIO2,I2C0_SDA)
3_G2: IC3.14 (B5), RASPBERRY-PI.P5_4 (GPIO29)
3_R1: IC3.18 (B1), RASPBERRY-PI.P5_5 (GPIO30)
3_R2: IC3.15 (B4), RASPBERRY-PI.P5_3 (GPIO28)
+3V3: IC1.1 (VDD), RASPBERRY-PI.P1_17 (3V3)
+5V: +5V.1, IC2.20 (VCC), IC3.20 (VCC), RASPBERRY-PI.P1_2 (5V), RASPBERRY-PI.P1_4 (5V), RASPBERRY-PI.P5_1 (5V)
A: IC3.11 (B8), RASPBERRY-PI.P1_24 (GPIO8,SPI0_CE0)
B: IC2.18 (B1), RASPBERRY-PI.P1_16 (GPIO23)
C: IC2.17 (B2), RASPBERRY-PI.P1_18 (GPIO24)
CL: IC1.12 (O), RASPBERRY-PI.P1_19 (GPIO10_MOSI)
CLOCK: IC2.15 (B4), RASPBERRY-PI.P1_26 (GPIO7,SPI0_CE1)
D: IC2.16 (B3), RASPBERRY-PI.P1_22 (GPIO25)
DCLK: IC1.6 (O), RASPBERRY-PI.P1_21 (GPIO9_MISO)
DE: IC1.15 (O), RASPBERRY-PI.P1_11 (GPIO17)
E: IC3.12 (B7), RASPBERRY-PI.P1_10 (GPIO15,UART0_RXD)
GND: +5V.2, C1.2, C2.2, C3.2, C4.2, C5.2, C6.2, HUB75.4, HUB75.16, IC1.8 (VSS), IC2.1 (DIR), IC2.10 (GND), IC2.19 (G), IC3.1 (DIR), IC3.10 (GND), IC3.19 (G), PINBALL.2, PINBALL.4, PINBALL.6, PINBALL.8, PINBALL.10, PINBALL.12, PINBALL.14, RASPBERRY-PI.P1_6 (GND), RASPBERRY-PI.P1_9 (GND), RASPBERRY-PI.P1_20 (GND), RASPBERRY-PI.P1_25 (GND), RASPBERRY-PI.P5_7 (GND), RASPBERRY-PI.P5_8 (GND)
unnamed: PINBALL.7, RN2.1
unnamed: PINBALL.5, RN2.3 (1)
unnamed: PINBALL.3, RN2.5 (1)
unnamed: PINBALL.1, RN2.7 (1)
unnamed: PINBALL.9, RN1.7 (1)
unnamed: PINBALL.11, RN1.5 (1)
OE: IC2.13 (B6), RASPBERRY-PI.P1_12 (GPIO18)
PIN_DMD_CL: C3.1, IC1.11 (I), RN2.2
PIN_DMD_DCLK: C2.1, IC1.7 (I), RN1.8 (2)
PIN_DMD_DE: C6.1, IC1.14 (I), RN2.8 (2)
PIN_DMD_RCLK: C4.1, IC1.5 (I), RN2.4 (2)
PIN_DMD_RD: C5.1, IC1.3 (I), RN2.6 (2)
PIN_DMD_SD: C1.1, IC1.9 (I), RN1.6 (2)
RCLK: IC1.4 (O), RASPBERRY-PI.P1_15 (GPIO22)
RD: IC1.2 (O), RASPBERRY-PI.P1_13 (GPIO27)
RGB_DMD_A: HUB75.9, IC3.9 (A8)
RGB_DMD_B: HUB75.10, IC2.2 (A1)
RGB_DMD_B0: HUB75.3, IC3.4 (A3)
RGB_DMD_B1: HUB75.7, IC3.7 (A6)
RGB_DMD_C: HUB75.11, IC2.3 (A2)
RGB_DMD_CLK: HUB75.13, IC2.5 (A4)
RGB_DMD_D: HUB75.12, IC2.4 (A3)
RGB_DMD_E: HUB75.8, IC3.8 (A7)
RGB_DMD_G0: HUB75.2, IC3.3 (A2)
RGB_DMD_G1: HUB75.6, IC3.6 (A5)
RGB_DMD_OE: HUB75.15, IC2.7 (A6)
RGB_DMD_R0: HUB75.1, IC3.2 (A1)
RGB_DMD_R1: HUB75.5, IC3.5 (A4)
RGB_DMD_STB: HUB75.14, IC2.6 (A5)
SD: IC1.10 (O), RASPBERRY-PI.P1_23 (GPIO11_SCLK)
STROBE: IC2.14 (B5), RASPBERRY-PI.P1_7 (GPIO4,GPCLK0)

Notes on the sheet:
real pinball input

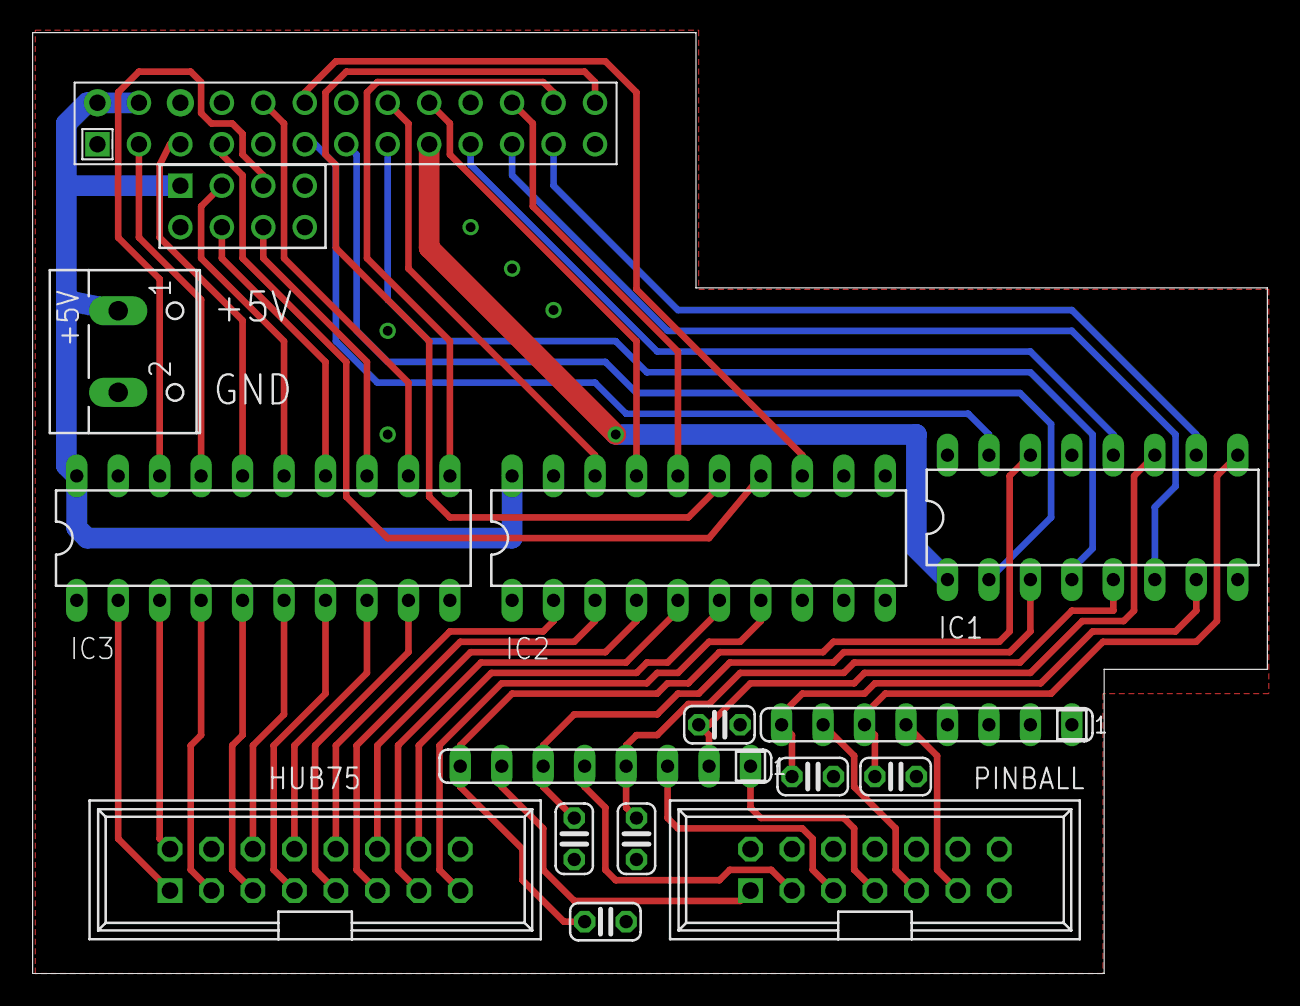
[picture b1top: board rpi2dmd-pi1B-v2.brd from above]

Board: 2 copper layers, 75.6 x 57.6 mm, 15 parts (0 on the bottom side), 49 nets.

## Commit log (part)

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2025-10-18 Fix dark album rows
2025-10-18 Fix overlapping artist name
2025-10-18 More real time song data
2025-10-18 More compact spacing
2025-10-18 Text wrap around
2025-10-18 Smaller text buffer and scroll hiccup fix
2025-10-18 Background thread for spotify requests
2025-10-18 Delay before scrolling
2025-10-18 Shorter wraparound spacing
2025-10-18 Shorter wraparound spacing for album
2025-10-18 Simple clock
2025-10-18 Fix font path again
2025-10-18 clock fixes
2025-10-18 Cleaner look
2025-10-18 Accurate time and all on one line
2025-10-18 Include day and date
2025-10-18 Reformat
2025-10-18 Another timezone fix and better formatting
2025-10-18 Formatting again
2025-10-18 Alignment
2025-10-18 Alignment again
2025-10-18 Font size
2025-10-18 Dynamic centering
2025-10-18 Weather display first pass
2025-10-18 Rapid updates
2025-10-18 Remove threading for better perf
2025-10-18 Perf
2025-10-19 Weather display updates
2025-10-19 Update spotify faster
2025-10-19 Faster updates
2025-10-19 Weather reformat
2025-10-19 Icon debugging
2025-10-19 Icon enhancements
2025-10-19 Move high temp down
2025-10-19 Reformatting
2025-10-19 Resize time
2025-10-19 New font
2025-10-19 Cmd line locale config
2025-10-19 Tattoo test
2025-10-19 Tattoo another pass
2025-10-19 Remove tattoo time
2025-10-19 Remove background
2025-10-19 Default values
2025-10-19 Stock tracker first pass
2025-10-19 Env key
2025-10-19 Env ignore
2025-10-19 Debug
2025-10-19 Font fix
2025-10-19 Font fix again
2025-10-19 Back to advanced
2025-10-19 Yahoo API
2025-10-19 Fix timing of display
2025-10-19 Test
2025-10-19 Simple case
2025-10-19 Smaller font and 2px padding
2025-10-19 Change values
2025-10-19 Right align
2025-10-19 Chart
2025-10-19 Chart fix
2025-10-19 Disable chart, debug
2025-10-19 Debug and historical data
2025-10-19 Debug and historical data again
2025-10-19 Fix deadlock
2025-10-19 Timeout issue
2025-10-19 64 days of history
2025-10-19 Chart infill
2025-10-19 Dynamically include trending stocks
2025-10-19 Smoother scrolling
2025-10-19 Threading to help with scroll lag
2025-10-19 Scroll slower
2025-10-19 Longer static text before scroll, quicker data refresh
2025-10-19 Fix chart blinking
2025-10-19 Blinking fix
2025-10-19 Chart disappear fix
2025-10-19 Chart debug
2025-10-19 Gif viewer
2025-10-19 Add url param for gif
2025-10-19 Fit gif to screen
2025-10-19 Fit by default
2025-10-19 Video player
2025-10-19 Video url
2025-10-19 Perf improvements
2025-10-20 Add weather icon mapping system and configuration files
    - Add map_weather_icons.py script for processing weather icons
    - Add .gitignore for assets directory
    - Add .gitattributes configuration
2025-10-20 Add processed weather icons for LED display
    - 18 weather icons optimized for 32x32 LED matrix
    - All OpenWeatherMap icon codes covered (01d-50n)
    - Icons resized and color-optimized for LED display visibility
2025-10-20 Add basic weather icons: Sun, Moon, and Stars
    - Add various sun icons (clear day conditions)
    - Add moon and star icons (clear night conditions)
    - High-quality source assets for weather icon mapping
2025-10-20 Reisze icons
2025-10-20 Alt sun
2025-10-20 Improve weather display layout: smaller city font and better time positioning
    - Add tiny 4x6 font for more compact city name display
    - Move time display to Y=5 for better clearance from 26x26 weather icons
    - Use tiny font for city name to reduce visual clutter
2025-10-20 Resize
2025-10-20 Reposition
2025-10-20 Overwrite icon
2025-10-20 Debug borders
2025-10-20 Draw time after icon
2025-10-20 Darken dull pixels
2025-10-20 Resize icon
2025-10-20 Rework images
2025-10-20 Dim pixel fix
2025-10-20 Center tmps
2025-10-20 Tests and readme
2025-10-20 Screen touchups
2025-10-20 Remove unnecessary extra info
2025-10-20 Param for time
2025-10-20 Param for time fix
2025-10-20 Lighter grey progress bar
2025-10-20 Status indicator
2025-10-20 Icon fixes
2025-10-20 Done font
2025-10-20 Subtitle
2025-10-20 Whitespace
2025-10-22 Fix imports
2025-10-22 Move remaining apps
2025-10-22 Consolidate shared functionality
2025-10-22 Refactor base matrix class:
2025-10-22 Fix font references
2025-10-22 Retro clock
2025-10-22 Change style of retro clock
2025-10-22 Background color and digit windows
2025-10-22 Brightness setting
2025-10-22 Stock display updates
2025-10-22 Color reference updates in stocks
2025-10-22 Small style tweaks
2025-10-22 Color update
2025-10-22 Time change animation
2025-10-22 Missing config
2025-10-22 Flip animation changes
2025-10-22 Flip animation update again
2025-10-22 Another go at the flip animation
2025-10-22 Brightness settings
2025-10-22 Remove traces of deprecated stock tracker
2025-10-22 Rename advanced-stock-tracker
2025-10-22 Fix stock display
2025-10-22 Right align text
2025-10-22 Right align text fix
2025-10-22 Font fixes
2025-10-23 Font fixes again please work
2025-10-23 Font fixes again please work pt 2
2025-10-23 Position updates
2025-10-23 Make chart bigger
2025-10-23 Comments
2025-10-23 Revert to simple time update
2025-10-23 Timezone support
2025-10-23 DRY timezone
2025-10-23 Timezone manager again
2025-10-23 Default to denver timezone
2025-10-23 Cleanup
2025-10-23 Timezone fix for real
2025-10-23 UTC-6 instead of -7
2025-10-25 Write a wrapper for Pillow.Image.getim()
2025-10-25 refactor on hardware
2025-10-25 Update removed ANTIALIAS constant to LANCZOS
2025-10-27 Refactor broken unsafe SetImagePillow()
2025-10-27 Remove extra pointer indirection
2025-10-27 remove unused var
2025-10-30 New DoubleZ multiplexer. Used for 64x32 HUB75 RGB with ICN2037BP chip.
2025-11-08 New DoubleZ multiplexer. Used for 64x32 HUB75 RGB with ICN2037BP chip. (#1819)
2025-11-26 Update README.md
    Fix
    https://github.com/hzeller/rpi-rgb-led-matrix/issues/1825
2025-11-27 Fix memory leak for color lookup (#1763)
    * add singleton lookup table
    * move method and change return type
    * make luminance_cie1931 private
2025-11-27 Reuse CreateFrameCanvas() in samples/gif-viewer.py
2025-11-27 Change thumbnail filter from ANTIALIAS to LANCZOS
2025-11-27 Update README.md on python support
2025-11-27 added link to https://www.acmesystems.it/HAT-A3
    replaces https://github.com/hzeller/rpi-rgb-led-matrix/pull/777
2025-11-27 Update README.md
    Mention https://github.com/hzeller/rpi-rgb-led-matrix/pull/1478/files until @ledvinap can give better documentation.
2025-11-27 show custom mapper
    fixes https://github.com/hzeller/rpi-rgb-led-matrix/issues/1732
2025-11-27 new issue template
2025-11-27 scripts to handle bugs
2025-11-27 files on how to handle bugs
2025-11-27 Rename README to .README
2025-11-28 Update runtext.py with more parameters
2025-12-02 chore: push local updates
2025-12-04 Upgrade TargetFramework to .NET 8.0
2025-12-09 Remove distutils over setuptools
2025-12-10 Add notes on parameters for streams
2025-12-10 Attempt to fix emoji in wiring.md
2025-12-10 Check to see if space really affected it
2025-12-11 Unify examples config
2025-12-11 Adding Interfaces
2025-12-11 Adding interface files
2025-12-11 Update README.md
    Python fork header mistakenly included, now removed.
    Basic information on installing Python bindings included under Python Support section.
2025-12-15 Add StackToRow mapper implementation (#1)
    * Add initial windmill mapper
    * Add new windmill
    * Add nearly working windmill
    * Slight fix
    * Fix x axis
    * Add working mapper
2025-12-16 Add example layout
2025-12-16 Ignore Visual Studio files
2025-12-16 Add powershell script to sync files with pi and build
2025-12-18 Add Visual Studio folder to gitignore
2025-12-18 Add sync script
2025-12-18 Add UID logging, allow passing filename as cmdline param
2025-12-19 Simplify filename prompt
2025-12-19 Declare options once, at start of program
2025-12-20 Set --led-no-drop-privs in Bindings
2025-12-22 Add additional multiplexing types to enum
2026-01-03 Set up tooling
2026-01-03 Revert "Add sync script"
    This reverts commit 40c4147ab6659039d7056fc17e5682d782070354.
2026-01-03 Minor README edit
2026-01-03 Make content-streamer functions externally accessible
2026-01-04 Add StreamReaderWrapper
2026-01-04 expose canvas field
2026-01-04 Update bindings to use lowercase_with_underscores. Fix cc file. Pass privs option. WORKING!!
2026-01-04 RenameStreamReaderWrapper to ContentStreamer
2026-01-04 Initial example
2026-01-04 Publish task targets specific csproj
2026-01-04 Ignore sln files (It will be auto-generated anyway)
2026-01-04 Tidy example
2026-01-04 Implement MatrixOptions.cs - all examples use same options
2026-01-04 Add CheckFileHeader to check if file is a valid stream
2026-01-04 Add ClearCanvas
2026-01-04 Revert out exposing ReadFileHeader - pointless as you need to new up a StreamReader to call it, by which point an exception would have been thrown if it was invalid
2026-01-04 Move MatrixOptions into examples folder
2026-01-04 Add instructions for Font example
2026-01-04 Add instructions for StreamPlayer
2026-01-04 Exclude example files from bindings project, not whole folder
2026-01-04 Remove redundant CheckFileHeader
2026-01-04 Move Clear from Content Streamer to Canvas, as it logically belongs there
2026-01-04 Expose required methods from API and create C# bindings for content-streamer
2026-01-04 Implement example using c# ContentStreamer
2026-01-04 Add tooling
2026-01-04 Change exclusions
2026-01-05 Remove redundant binding to clear
2026-01-05 Change holdTimeUs from ref to out
2026-01-07 Remove MatrixOptions
2026-01-07 Remove superfluous ImageSharp reference
2026-01-08 initial attempt, open not happy
2026-01-08 Fix issue with open
2026-01-08 Revert needlessly modified files back
2026-01-09 Simplify member access, remove redundant assignment
2026-01-10 Add IsCompatible to content-streamer
2026-01-11 Compiler optimization (Native CPU arch compile params)
2026-01-11 Throw ObjectDisposedException if StreamIO is not initialized
2026-01-12 Fixed random warning messages during build step
2026-01-12 Fix warning on build
2026-01-13 Add VSCode tasks for cross-compilation for windows
2026-01-15 Added a central bash runner script to improve flickering
2026-01-24 Changes made in response to comments. Removed interfaces for now as need further discussion
2026-01-27 Trying scikit-build-core.
2026-01-27 In-progress scikit-build-core progress. It's getting close....
2026-01-27 Add support for Raspberry Pi CM4S model
2026-02-10 video-viewer: make compile in modern times.
2026-02-10 Modernize led-image-viewer random shuffle use.
2026-02-10 Make it possible to choose compiler environment.
2026-02-10 Configure lto and march options at a central place.
    config.mk contains what is necessary (things are dependent on
    compiler, so make it simple to deal with it once)
2026-02-10 PixelDesignatorMap: use std::vector instead of raw buffer.
2026-02-10 Squash warning about ignoring write() return value.
2026-02-10 Now that we distinguish compilers, set lto to 2 again.
2026-03-06 Remove the Python make checks from Github CI.
2026-03-06 Remove python from make clean.
2026-03-17 Added RT Kernel
    FIX: https://github.com/hzeller/rpi-rgb-led-matrix/issues/1754
2026-03-17 Update README.md to point to RT kernel documentation
    Fix https://github.com/hzeller/rpi-rgb-led-matrix/issues/1754
2026-03-23 Revert C# readme to original state
2026-03-24 Real Time Kernel Documentation Update
2026-03-27 Fix warning: cc1plus: warning: ‘-Werror=’ argument ‘-Werror=implicit-function-declaration’ is not valid for C++
2026-03-31 Added MeasureText function
2026-03-31 RT Kernel Documentation Update - Pi 3 / Zero 2W guide steps.
2026-04-05 Added adafruit active-3 board
2026-04-05 Modify Python installation commands in README
    Updated Python installation instructions in README.
2026-04-07 Update InternalRGBLedMatrixOptions.cs
    Fix https://github.com/hzeller/rpi-rgb-led-matrix/issues/1867
2026-04-25 Raspberry Pi5 Support v0.06
